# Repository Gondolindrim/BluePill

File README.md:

# Acheron Blue Pill

See [this page](https://gondolindrim.github.io/AcheronDocs/bluepill/intro.html) for the Acheron Blue Pill documentation.

## Copyright notice

This project is released under the Acheron Open-Hardware License V1.1. For the license, please refer to the LICENCE.md file.

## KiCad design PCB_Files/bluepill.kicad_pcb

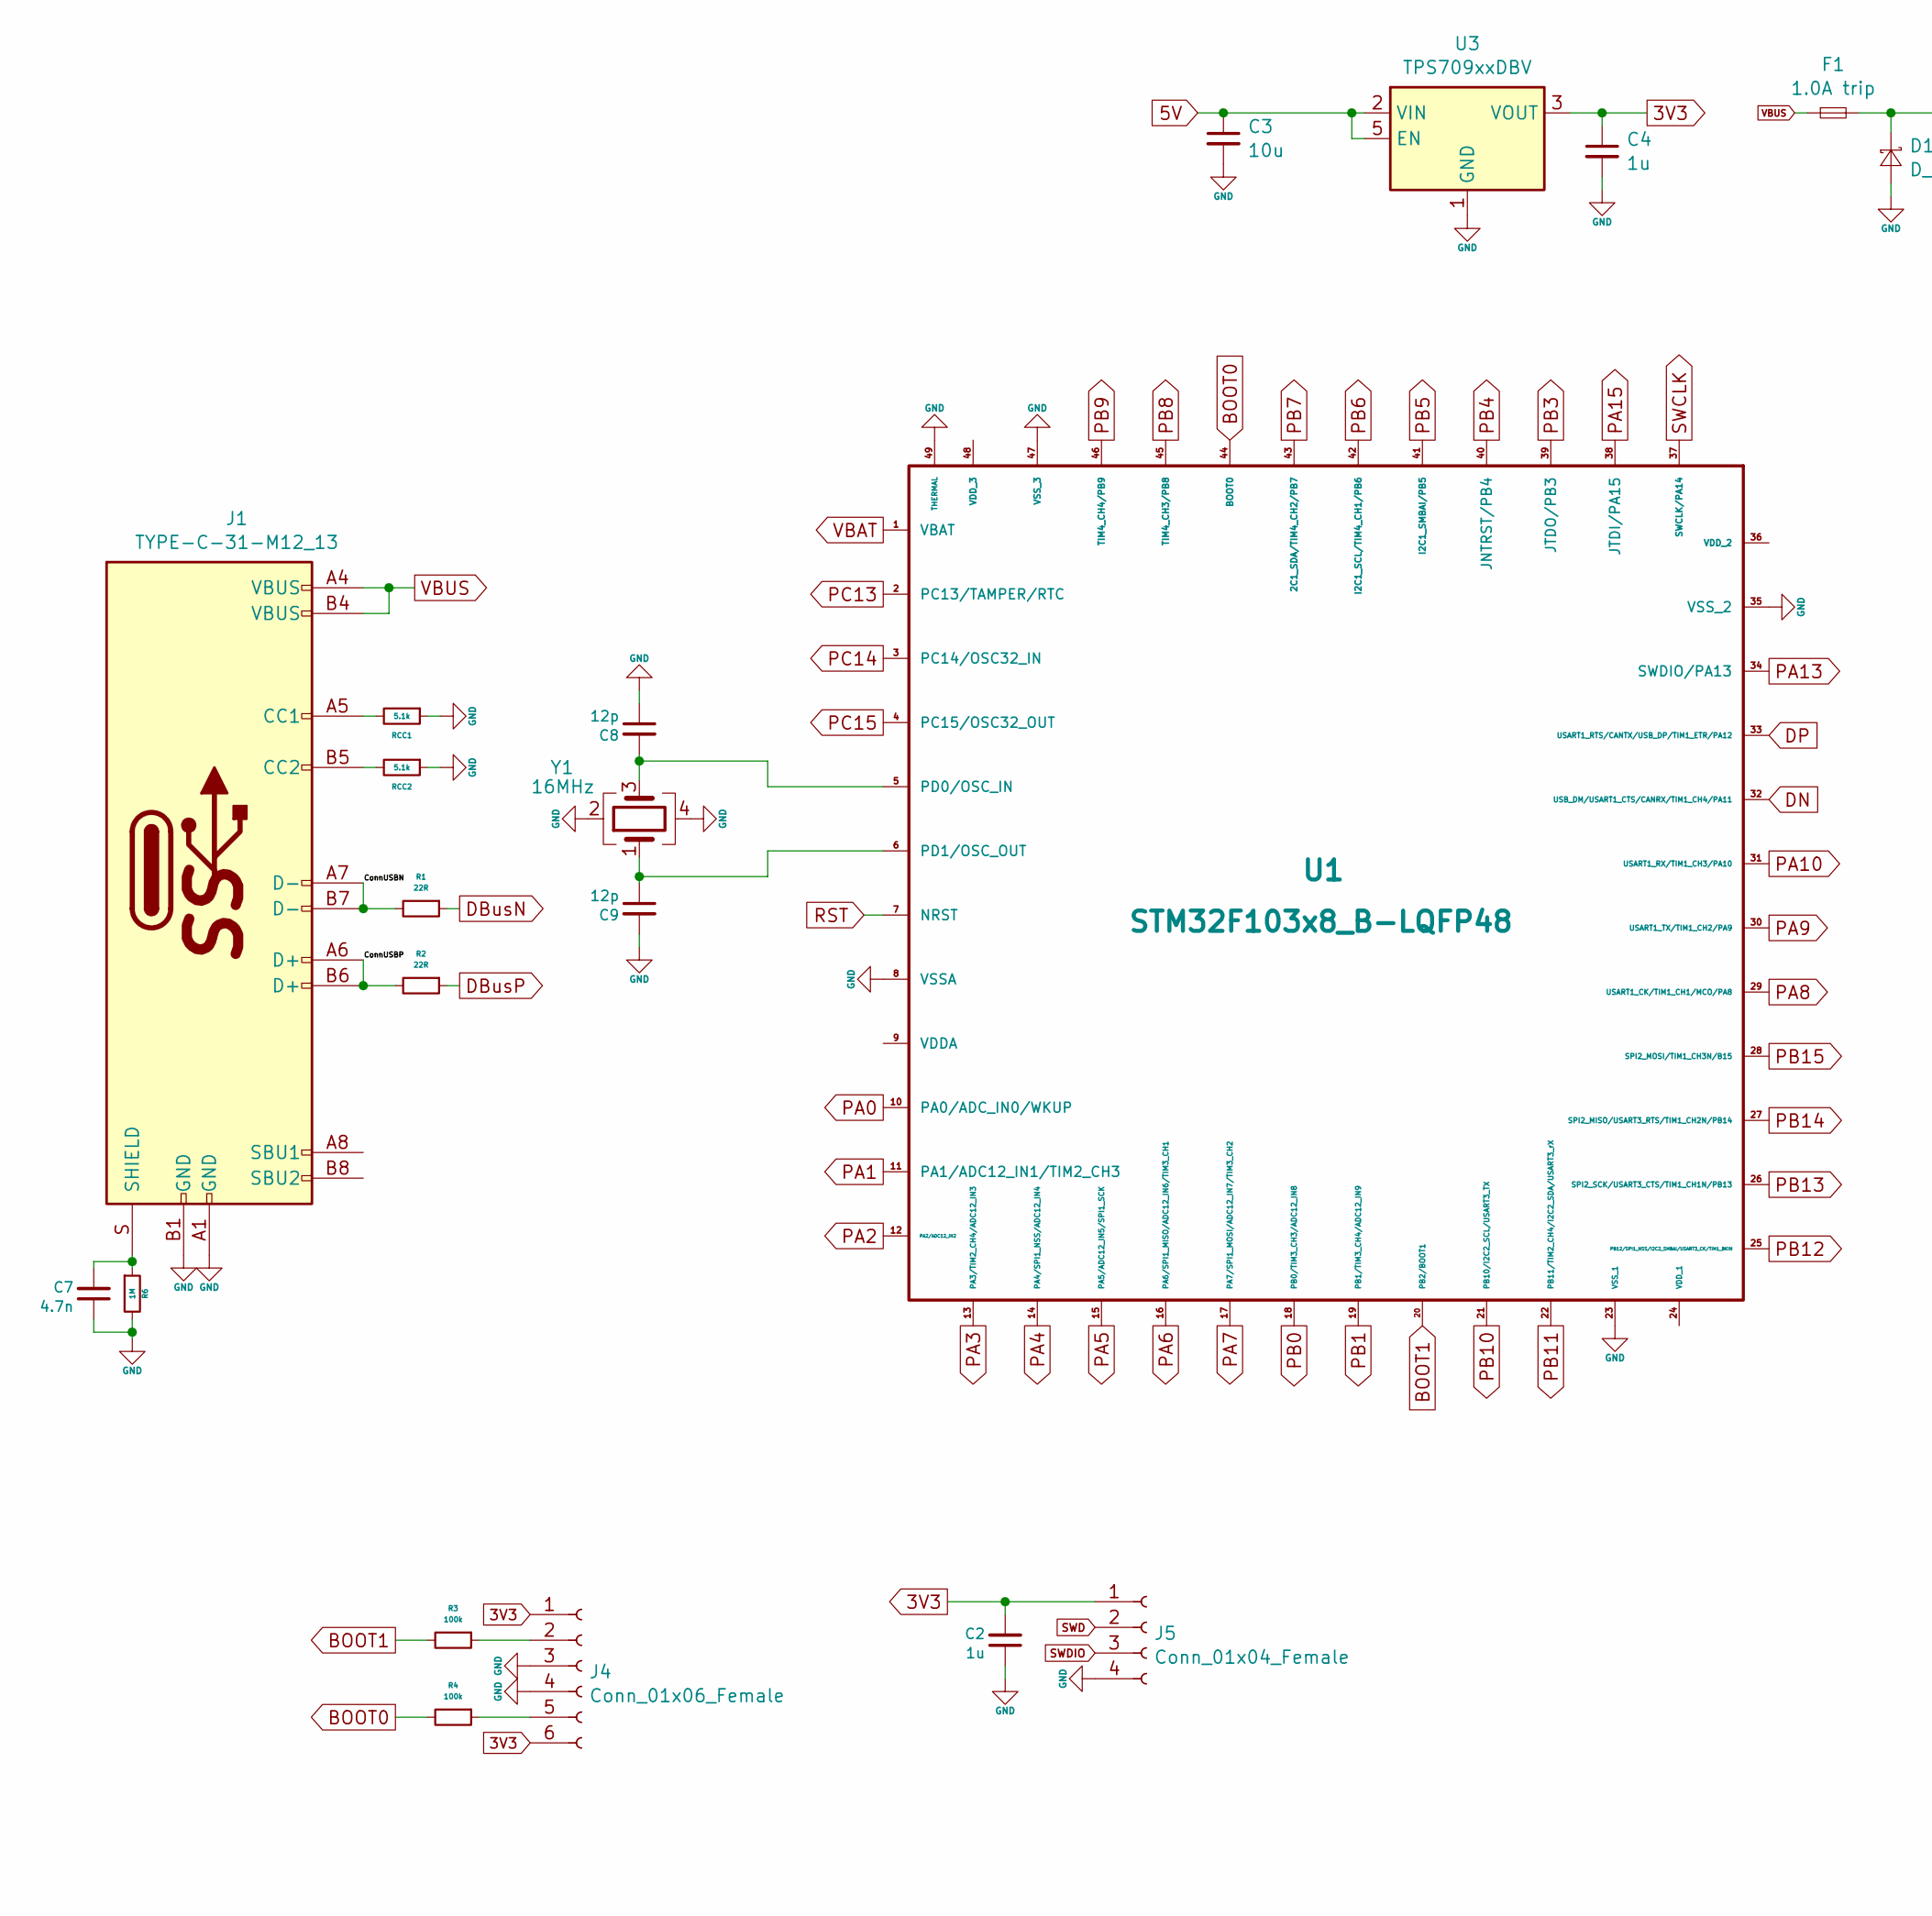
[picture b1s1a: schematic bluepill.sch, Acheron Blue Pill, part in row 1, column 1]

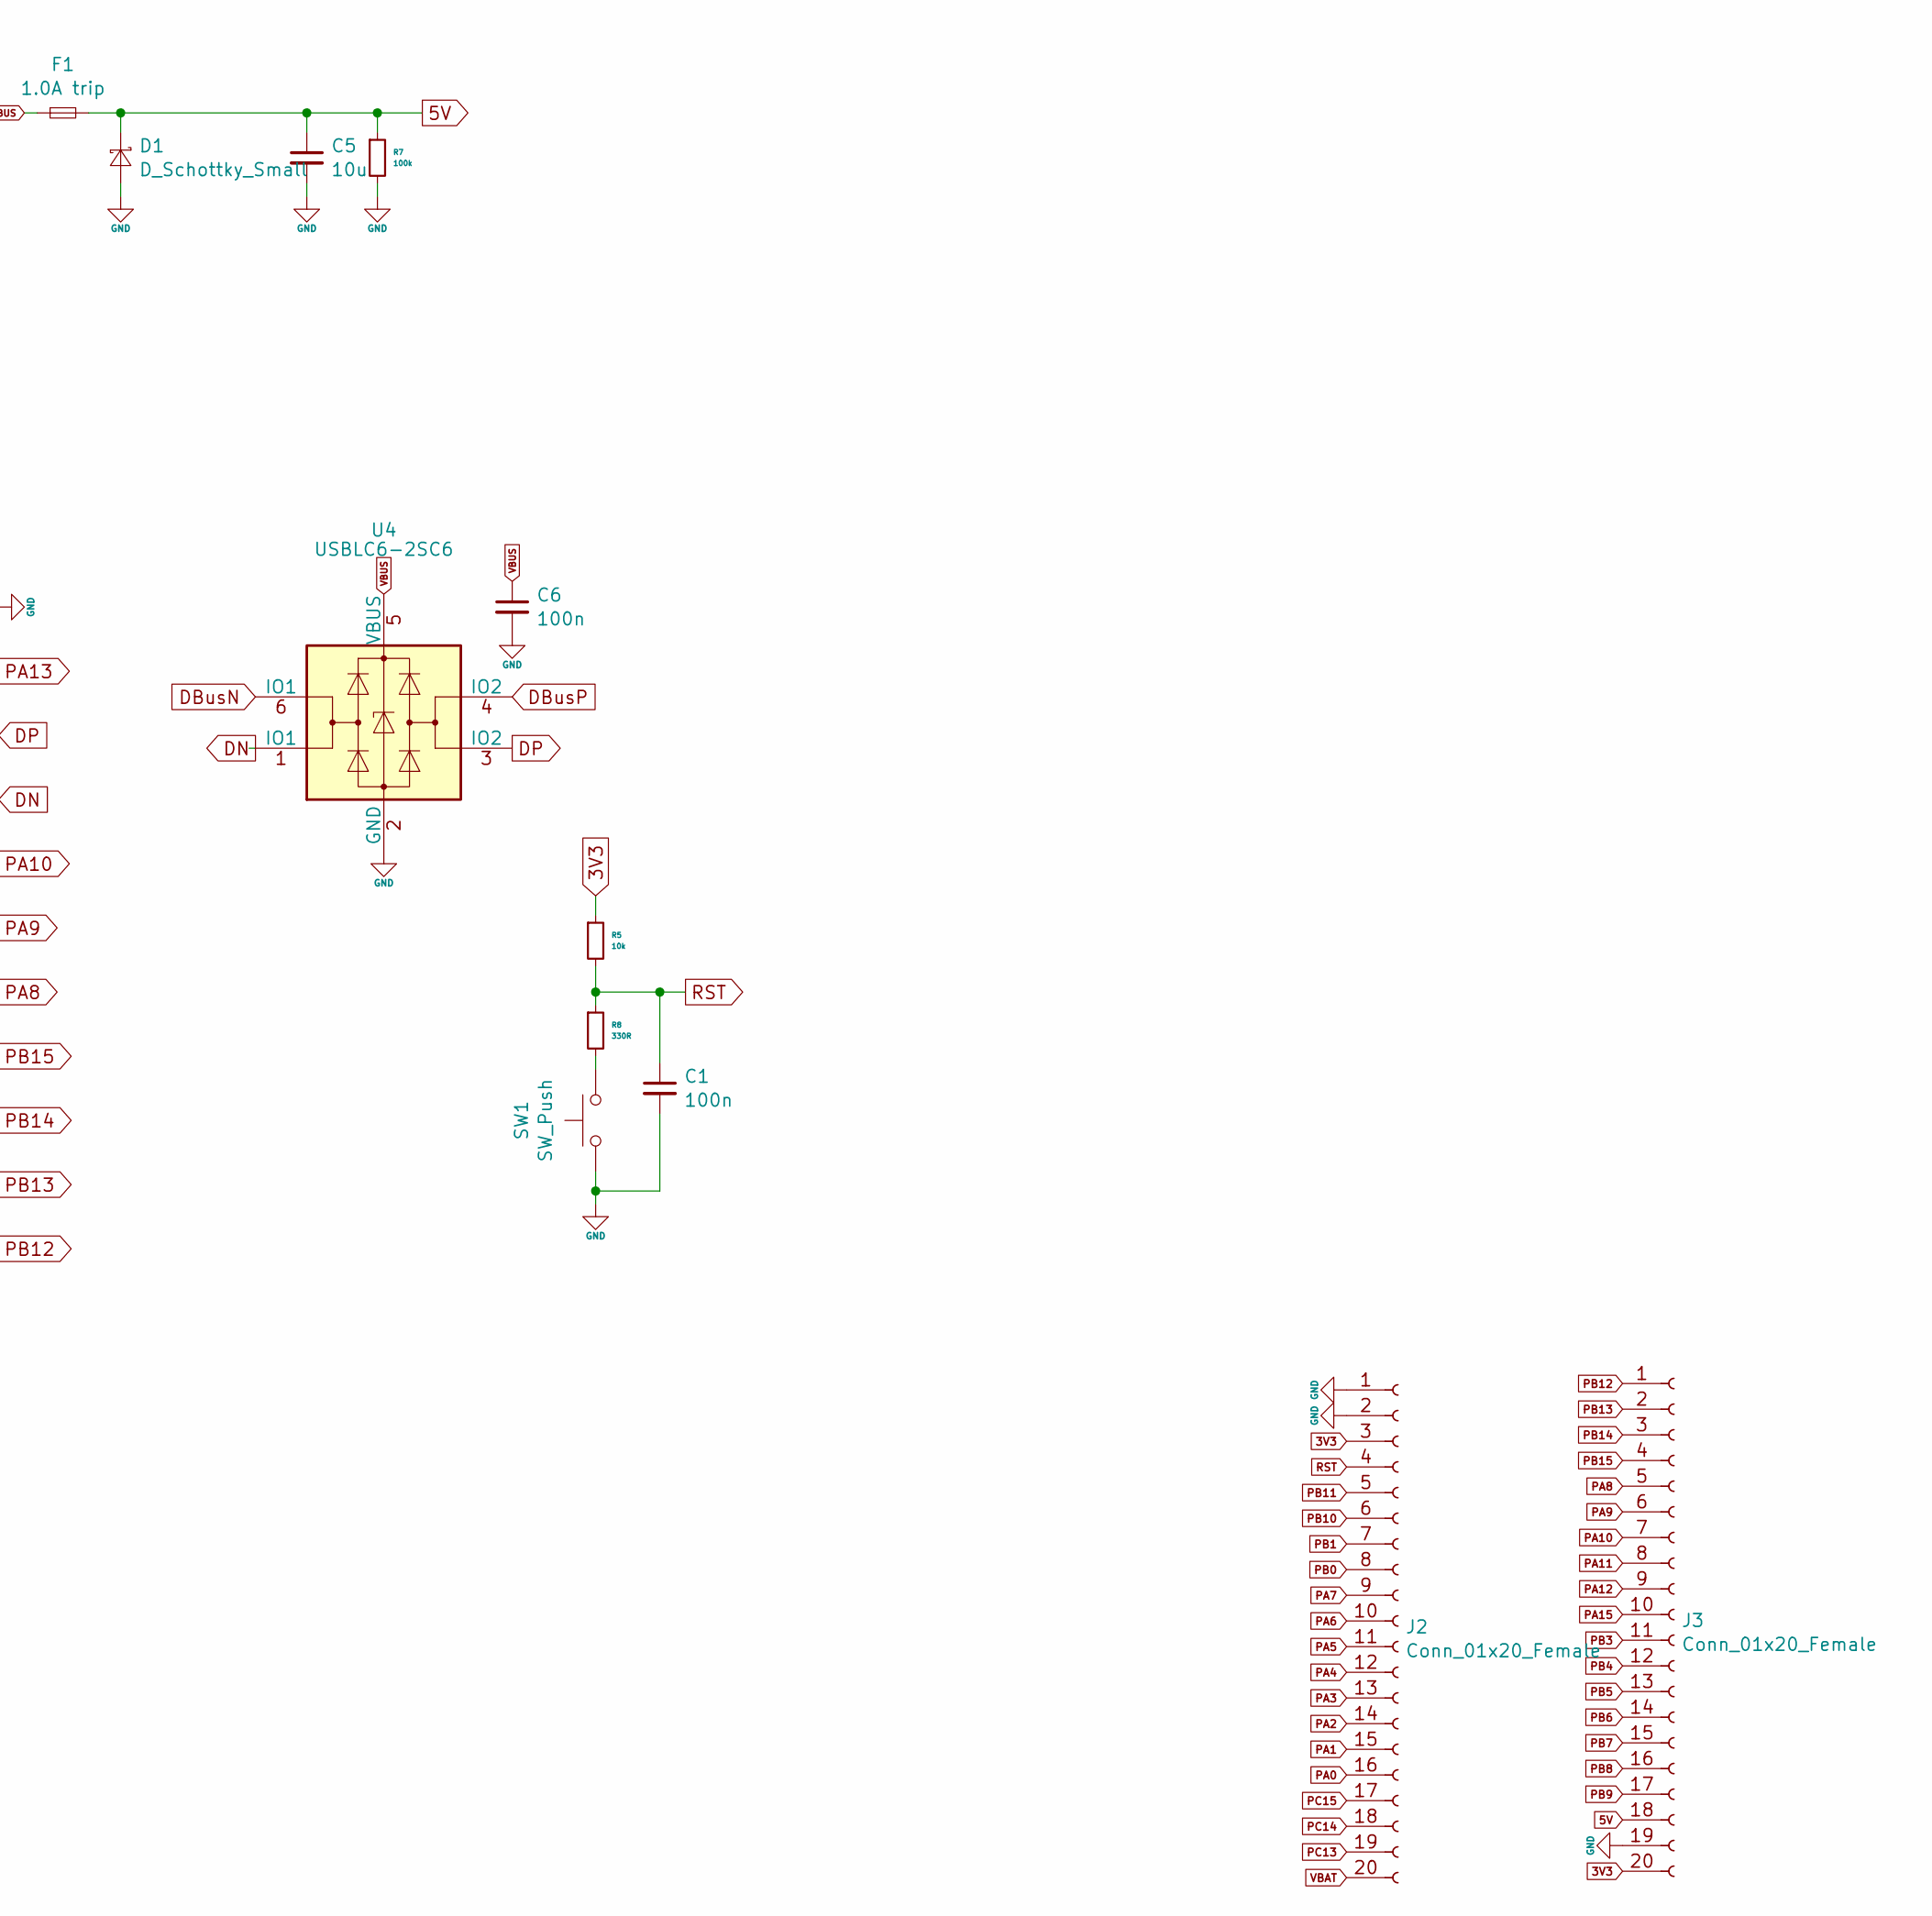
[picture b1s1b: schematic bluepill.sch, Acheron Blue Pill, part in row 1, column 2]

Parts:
C1, C6: 100n; C_0402_1005Metric
C2, C4: 1u; C_0402_1005Metric
C3, C5: 10u; C_0402_1005Metric
C7: 4.7n; C_0402_1005Metric
C8, C9: 12p; C_0402_1005Metric
D1: D_Schottky_Small; D_0603_1608Metric
F1: 1.0A trip; Fuse_0603_1608Metric
J1: TYPE-C-31-M12_13; TYPE-C-31-M-12
J2, J3: Conn_01x20_Female; HEADER_20PIN
J4: Conn_01x06_Female; HEADER_6PIN_HORIZONTAL
J5: Conn_01x04_Female; HEADER_4PIN
R1, R2: 22R; R_0402_1005Metric
R3, R4, R7: 100k; R_0402_1005Metric
R5: 10k; R_0402_1005Metric
R6: 1M; R_0402_1005Metric
R8: 330R; R_0402_1005Metric
RCC1, RCC2: 5.1k; R_0402_1005Metric
SW1: SW_Push; smdPushBtn
U1: STM32F103x8_B-LQFP48; UQFN-48-1EP_6x6mm_P0.4mm_EP4.62x4.62mm
U3: TPS709xxDBV; SOT-23-5
U4: USBLC6-2SC6; SOT-23-6
Y1: 16MHz; Crystal_SMD_2016-4Pin_2.0x1.6mm

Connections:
3V3: C2.2, C4.1, J2.3, J3.20, J4.1, J4.6, J5.1, R5.1, U3.3 (VOUT)
5V: C3.1, C5.1, D1.1 (K), F1.2, J3.18, R7.1, U3.2 (VIN), U3.5 (EN)
/ConnUSBN: J1.A7 (D-), J1.B7 (D-), R1.2
/ConnUSBP: J1.A6 (D+), J1.B6 (D+), R2.2
BOOT0: R4.2, U1.44 (BOOT0)
BOOT1: R3.2, U1.20 (PB2/BOOT1)
DBusN: R1.1, U4.6 (IO1)
DBusP: R2.1, U4.4 (IO2)
DN: U1.32 (USB_DM/USART1_CTS/CANRX/TIM1_CH4/PA11), U4.1 (IO1)
DP: U1.33 (USART1_RTS/CANTX/USB_DP/TIM1_ETR/PA12), U4.3 (IO2)
GND: C1.2, C2.1, C3.2, C4.2, C5.2, C6.2, C7.1, C8.1, C9.2, D1.2 (A), J1.A1 (GND), J1.B1 (GND), J2.1, J2.2, J3.19, J4.3, J4.4, J5.4, R6.2, R7.2, RCC1.1, RCC2.1, SW1.1, U1.8 (VSSA), U1.23 (VSS_1), U1.35 (VSS_2), U1.47 (VSS_3), U1.49 (THERMAL), U3.1 (GND), U4.2 (GND), Y1.2, Y1.4
unnamed: C7.2, J1.S (SHIELD), R6.1
unnamed: C8.2, U1.5 (PD0/OSC_IN), Y1.3
unnamed: C9.1, U1.6 (PD1/OSC_OUT), Y1.1
unnamed: J1.A5 (CC1), RCC1.2
unnamed: J1.B5 (CC2), RCC2.2
unnamed: J4.2, R3.1
unnamed: J4.5, R4.1
unnamed: R8.2, SW1.2
PA0: J2.16, U1.10 (PA0/ADC_IN0/WKUP)
PA1: J2.15, U1.11 (PA1/ADC12_IN1/TIM2_CH3)
PA2: J2.14, U1.12 (PA2/ADC12_IN2)
PA3: J2.13, U1.13 (PA3/TIM2_CH4/ADC12_IN3)
PA4: J2.12, U1.14 (PA4/SPI1_NSS/ADC12_IN4)
PA5: J2.11, U1.15 (PA5/ADC12_IN5/SPI1_SCK)
PA6: J2.10, U1.16 (PA6/SPI1_MISO/ADC12_IN6/TIM3_CH1)
PA7: J2.9, U1.17 (PA7/SPI1_MOSI/ADC12_IN7/TIM3_CH2)
PA8: J3.5, U1.29 (USART1_CK/TIM1_CH1/MCO/PA8)
PA9: J3.6, U1.30 (USART1_TX/TIM1_CH2/PA9)
PA10: J3.7, U1.31 (USART1_RX/TIM1_CH3/PA10)
PA11: J3.8
PA12: J3.9
PA13: U1.34 (SWDIO/PA13)
PA15: J3.10, U1.38 (JTDI/PA15)
PB0: J2.8, U1.18 (PB0/TIM3_CH3/ADC12_IN8)
PB1: J2.7, U1.19 (PB1/TIM3_CH4/ADC12_IN9)
PB3: J3.11, U1.39 (JTDO/PB3)
PB4: J3.12, U1.40 (JNTRST/PB4)
PB5: J3.13, U1.41 (I2C1_SMBAI/PB5)
PB6: J3.14, U1.42 (I2C1_SCL/TIM4_CH1/PB6)
PB7: J3.15, U1.43 (2C1_SDA/TIM4_CH2/PB7)
PB8: J3.16, U1.45 (TIM4_CH3/PB8)
PB9: J3.17, U1.46 (TIM4_CH4/PB9)
PB10: J2.6, U1.21 (PB10/I2C2_SCL/USART3_TX)
PB11: J2.5, U1.22 (PB11/TIM2_CH4/I2C2_SDA/USART3_rX)
PB12: J3.1, U1.25 (PB12/SPI1_NSS/I2C2_SMBAI/USART3_CK/TIM1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)
PB13: J3.2, U1.26 (SPI2_SCK/USART3_CTS/TIM1_CH1N/PB13)
PB14: J3.3, U1.27 (SPI2_MISO/USART3_RTS/TIM1_CH2N/PB14)
PB15: J3.4, U1.28 (SPI2_MOSI/TIM1_CH3N/B15)
PC13: J2.19, U1.2 (PC13/TAMPER/RTC)
PC14: J2.18, U1.3 (PC14/OSC32_IN)
PC15: J2.17, U1.4 (PC15/OSC32_OUT)
RST: C1.1, J2.4, R5.2, R8.1, U1.7 (NRST)
SWCLK: U1.37 (SWCLK/PA14)
SWD: J5.2
SWDIO: J5.3
VBAT: J2.20, U1.1 (VBAT)
VBUS: C6.1, F1.1, J1.A4 (VBUS), J1.B4 (VBUS), U4.5 (VBUS)

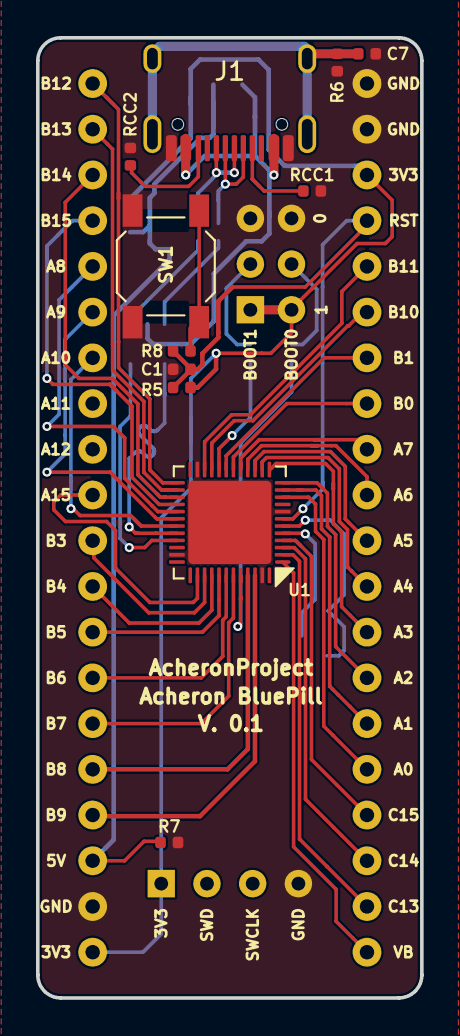
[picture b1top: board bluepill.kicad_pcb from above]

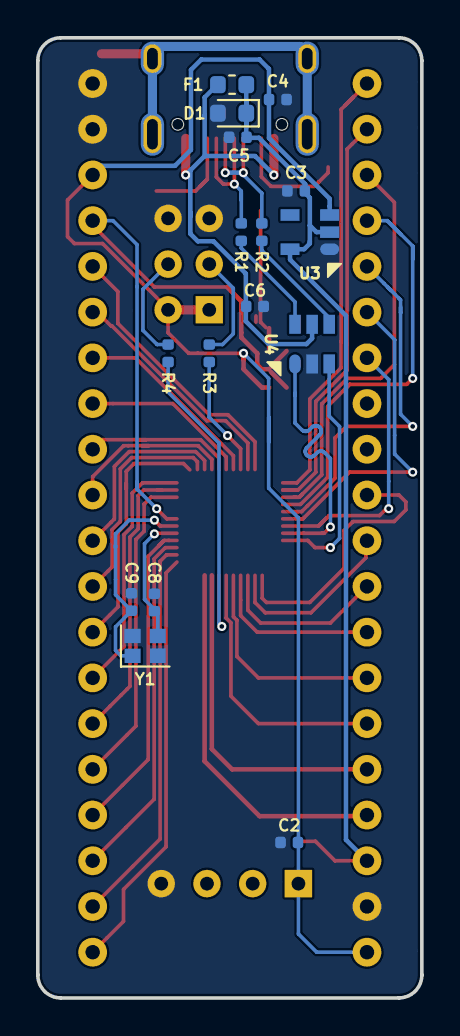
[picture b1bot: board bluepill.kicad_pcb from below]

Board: 2 copper layers, 21.3 x 53.3 mm, 31 parts (16 on the bottom side), 52 nets.

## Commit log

2019-08-26 Add initial PCB edges and connectors
    - PCB edges were added, along with pin header connectors and reset button, and USB connector
2019-09-17 Further tracing
2019-09-17 Added series resistor in reset net
2019-09-18 Further routing
